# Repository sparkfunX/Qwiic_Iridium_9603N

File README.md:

# Qwiic Iridium 9603N

Iridium 9603N in Qwiic format (with I2C connectivity)

[Qwiic Iridium 9603N (SPX-16394)](https://www.sparkfun.com/products/16394)

## Repository Contents

- **/Hardware** - Eagle PCB, SCH and LBR design files
- **/Firmware** - Arduino code which comes pre-programmed onto the board
- **LEARN.md** contains a description of the Qwiic Iridium 9603N hardware
- **LICENSE.md** contains the licence information

## Arduino Examples

You will find a complete set of Arduino Examples for the Qwiic Iridium 9603N built into the [SparkFun IridiumSBD I2C Arduino Library](https://github.com/sparkfun/SparkFun_IridiumSBD_I2C_Arduino_Library).
Look for the [I2C_Examples__Qwiic_Iridium](https://github.com/sparkfun/SparkFun_IridiumSBD_I2C_Arduino_Library/tree/master/examples).

## Acknowledgements

This project relies upon [Spence Konde's ATTinyCore](https://github.com/SpenceKonde/ATTinyCore) for the ATtiny841.
Spence's work is gratefully acknowledged.

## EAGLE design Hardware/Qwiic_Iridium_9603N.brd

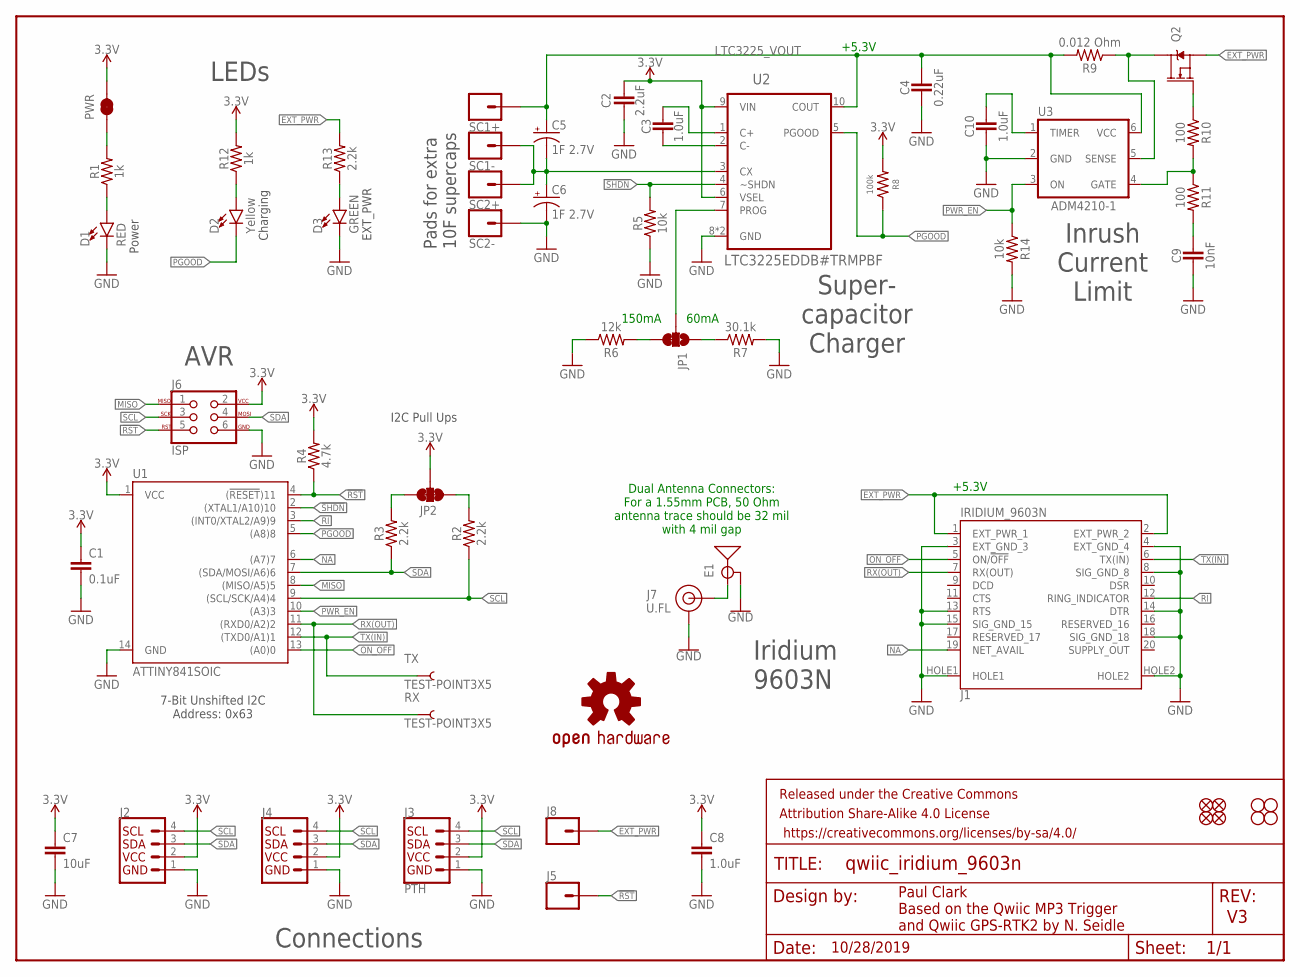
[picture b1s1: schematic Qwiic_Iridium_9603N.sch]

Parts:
C1: 0.1uF; 0603
C2: 2.2uF; 0603
C3, C8, C10: 1.0uF; 0603
C4: 0.22uF; 0603
C5, C6: 1F 2.7V; CPOL-RADIAL-1F-2.7V
C7: 10uF; 0603
C9: 10nF; 0603
D1: RED; LED-0603
D2: Yellow; LED-0603
D3: GREEN; LED-0603
E1: ANTENNA-GROUNDEDEDGE_SMA; SMA-EDGE
FRAME1: FRAME-LETTER; CREATIVE_COMMONS
J1: IRIDIUM_9603N
J2, J4: QWIIC_CONNECTORJS-1MM; JST04_1MM_RA
J3: PTH; 1X04_NO_SILK
J5, J8: CONN_01PTH_NO_SILK_YES_STOP; 1X01_NO_SILK
J6: ISP; 2X3_TEST_POINTS
J7: U.FL
JP1: JUMPER-SMT_3_1-NC_TRACE_SILK; SMT-JUMPER_3_1-NC_TRACE_SILK
JP2: JUMPER-SMT_3_2-NC_TRACE_SILK; SMT-JUMPER_3_2-NC_TRACE_SILK
JP3, JP4, JP9, JP10: STAND-OFF
JP5, JP6, JP7, JP8: FIDUCIAL1X2; FIDUCIAL-1X2
LOGO1: OSHW-LOGOMINI; OSHW-LOGO-MINI
PWR: JUMPER-SMT_2_NC_TRACE_SILK; SMT-JUMPER_2_NC_TRACE_SILK
Q2: 5.8A/30V/35mΩ; SOT23-3
R1, R12: 1k; 0603
R2, R3, R13: 2.2k; 0603
R4: 4.7k; 0603
R5, R14: 10k; 0603
R6: 12k; 0603
R7: 30.1k; 0603
R8: 100k; 0603
R9: 0.012 Ohm; 0603
R10, R11: 100; 0603
RX: TEST-POINT3X5; PAD.03X.05
SC1+, SC1-, SC2+, SC2-: CONN_01PTH_NO_SILK_YES_STOP; 1X01_NO_SILK
TX: TEST-POINT3X5; PAD.03X.05
U1: ATTINY841SOIC; ATTINY841
U2: LTC3225EDDB#TRMPBF; DFN300X200-10L
U3: ADM4210-1; TSOT6

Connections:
3.3V: C1.1, C2.1, C7.1, C8.1, J2.2, J3.2 (VCC), J4.2, J6.2, JP2.2, PWR.2, R4.2, R8.2, R12.2, U1.1 (VCC), U2.6 (VSEL), U2.9 (VIN)
!RST: J5.1, J6.5, R4.1, U1.4 ((!RESET!)11)
!SHDN: R5.2, U1.2 ((XTAL1/A10)10), U2.4 (~SHDN)
EXT_PWR: J1.1 (EXT_PWR_1), J1.2 (EXT_PWR_2), J8.1, Q2.2 (S), R13.2
GND: C1.2, C2.2, C4.2, C6.-, C7.2, C8.2, C9.2, C10.2, D1.C, D3.C, E1.GND@0 (GND), E1.GND@1 (GND), E1.GND@2 (GND), E1.GND@3 (GND), J1.3 (EXT_GND_3), J1.4 (EXT_GND_4), J1.8 (SIG_GND_8), J1.13 (RTS), J1.14 (DTR), J1.15 (SIG_GND_15), J1.18 (SIG_GND_18), J1.HOLE1, J1.HOLE2, J2.1, J3.1 (GND), J4.1, J6.6, J7.1 (GND), J7.2 (GND), R5.1, R6.1, R7.2, R14.2, SC2-.1, U1.14 (GND), U2.8 (GND), U2.11 (GND), U3.2 (GND)
LTC3225_VOUT: C4.1, C5.+, R9.2, SC1+.1, U2.10 (COUT), U3.6 (VCC)
MISO: J6.1, U1.8 ((MISO/A5)5)
unnamed: C5.-, C6.+, SC1-.1, SC2+.1, U2.3 (CX)
unnamed: JP1.3, R6.2
unnamed: D1.A, R1.1
unnamed: JP1.1, R7.1
unnamed: D2.A, R12.1
unnamed: D3.A, R13.1
unnamed: E1.SIG (SIGNAL), J7.FEED (SIGNAL)
unnamed: Q2.3 (D), R9.1, U3.5 (SENSE)
unnamed: C3.2, U2.2 (C-)
unnamed: C3.1, U2.1 (C+)
unnamed: JP1.2, U2.7 (PROG)
unnamed: Q2.1 (G), R10.1
unnamed: R10.2, R11.1, U3.4 (GATE)
unnamed: C9.1, R11.2
unnamed: C10.1, U3.1 (TIMER)
unnamed: PWR.1, R1.2
NA: J1.19 (NET_AVAIL), U1.6 ((A7)7)
ON_OFF: J1.5 (ON/!OFF!), U1.13 ((A0)0)
PGOOD: D2.C, R8.1, U1.5 ((A8)8), U2.5 (PGOOD)
PWR_EN: R14.1, U1.10 ((A3)3), U3.3 (ON)
RI: J1.12 (RING_INDICATOR), U1.3 ((INT0/XTAL2/A9)9)
RX(OUT): J1.7 (RX(OUT)), RX.P$1, U1.11 ((RXD0/A2)2)
SCL: J2.4, J3.4 (SCL), J4.4, J6.3, R2.1, U1.9 ((SCL/SCK/A4)4)
SCL_PU1: JP2.1, R2.2
SDA: J2.3, J3.3 (SDA), J4.3, J6.4, R3.1, U1.7 ((SDA/MOSI/A6)6)
SDA_PU1: JP2.3, R3.2
TX(IN): J1.6 (TX(IN)), TX.P$1, U1.12 ((TXD0/A1)1)

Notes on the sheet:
Paul Clark Based on the Qwiic MP3 Trigger and Qwiic GPS-RTK2 by N. Seidle
Power
7-Bit Unshifted I2C Address: 0x63
I2C Pull Ups
AVR
Connections
+5.3V
150mA
60mA
Pads for extra 10F supercaps
Super- capacitor Charger
Charging
EXT_PWR
Iridium 9603N
Dual Antenna Connectors: For a 1.55mm PCB, 50 Ohm antenna trace should be 32 mil with 4 mil gap
LEDs
Inrush Current Limit
10/28/2019

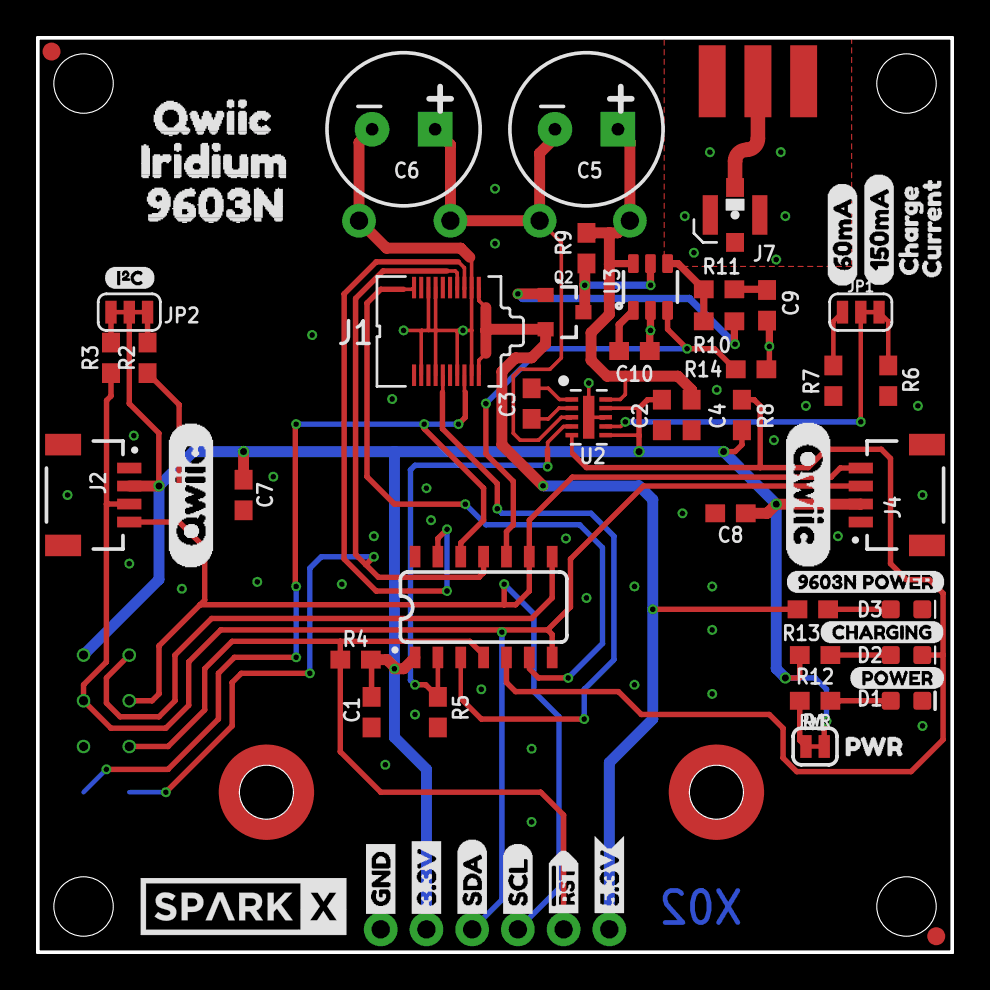
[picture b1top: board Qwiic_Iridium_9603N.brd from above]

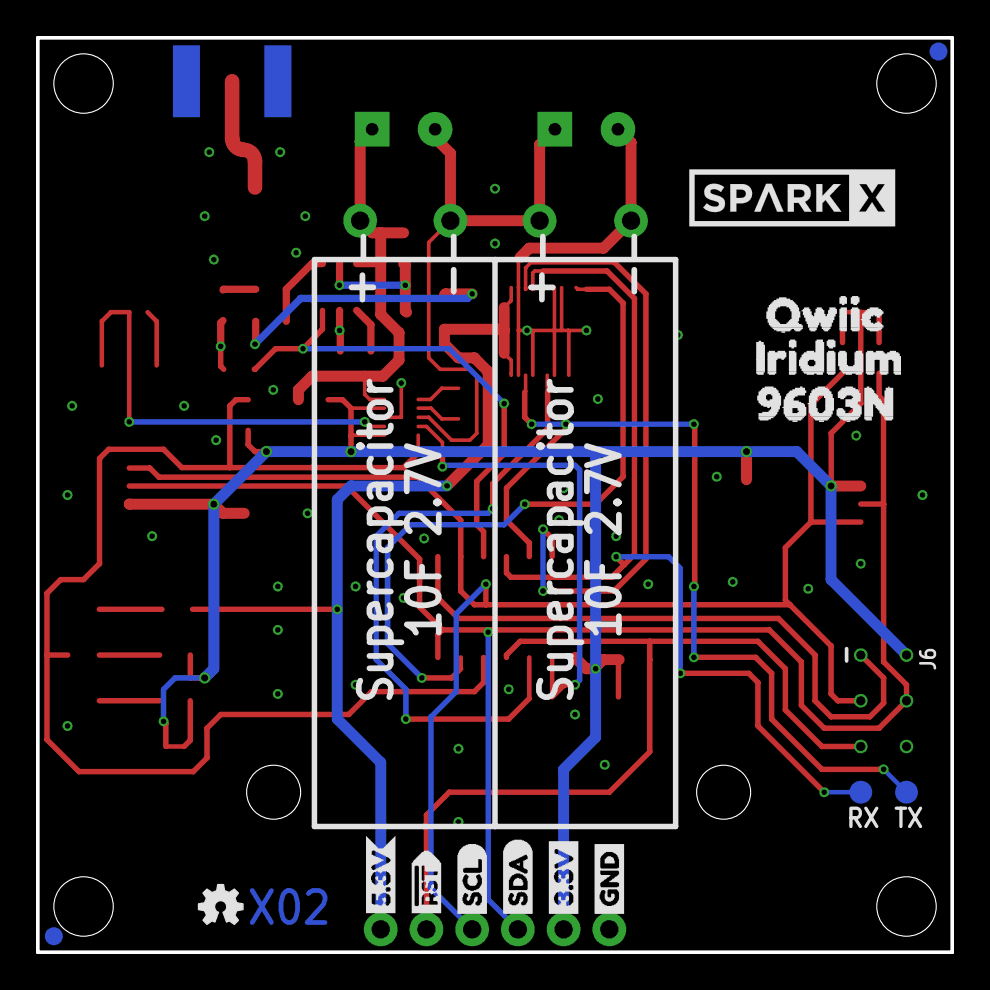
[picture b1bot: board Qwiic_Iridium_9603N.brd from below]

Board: 2 copper layers, 50.8 x 50.8 mm, 90 parts (16 on the bottom side), 34 nets.

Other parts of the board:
U$1: 60MA0
U$2: POWER0
U$3, U$22: GND1
U$4, U$21: 3#3V2
U$5, U$27: SDA8
U$6, U$26: SCL9
U$7, U$16: RST#-[>
U$8: I_SUPER2_C-()-03
U$9: CHARGING0
U$10: 9603N_POWER0
U$11, U$32: 5#3V0
U$12, U$17, U$23, U$25: QWIIC0
U$13: 150MA0
U$14: CHARGE0
U$15: CURRENT0
U$18, U$19: IRIDIUM0
U$20, U$24: 9603N0
U$29, U$30: SPARKX-LARGE
U$31: _PWR1

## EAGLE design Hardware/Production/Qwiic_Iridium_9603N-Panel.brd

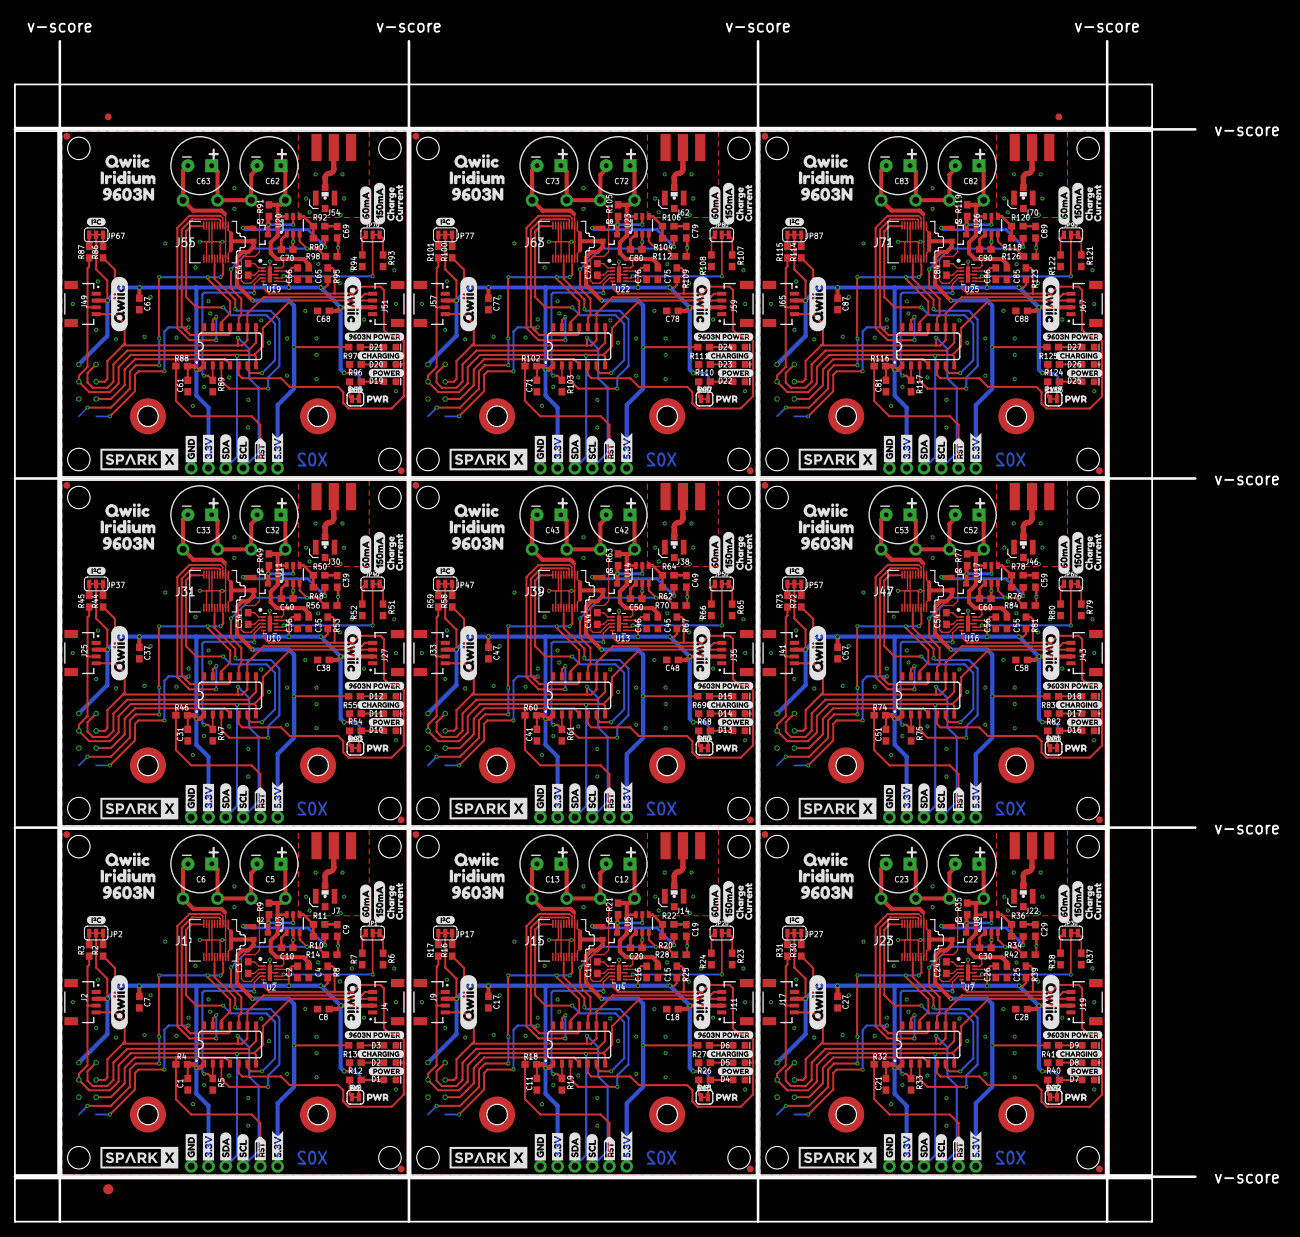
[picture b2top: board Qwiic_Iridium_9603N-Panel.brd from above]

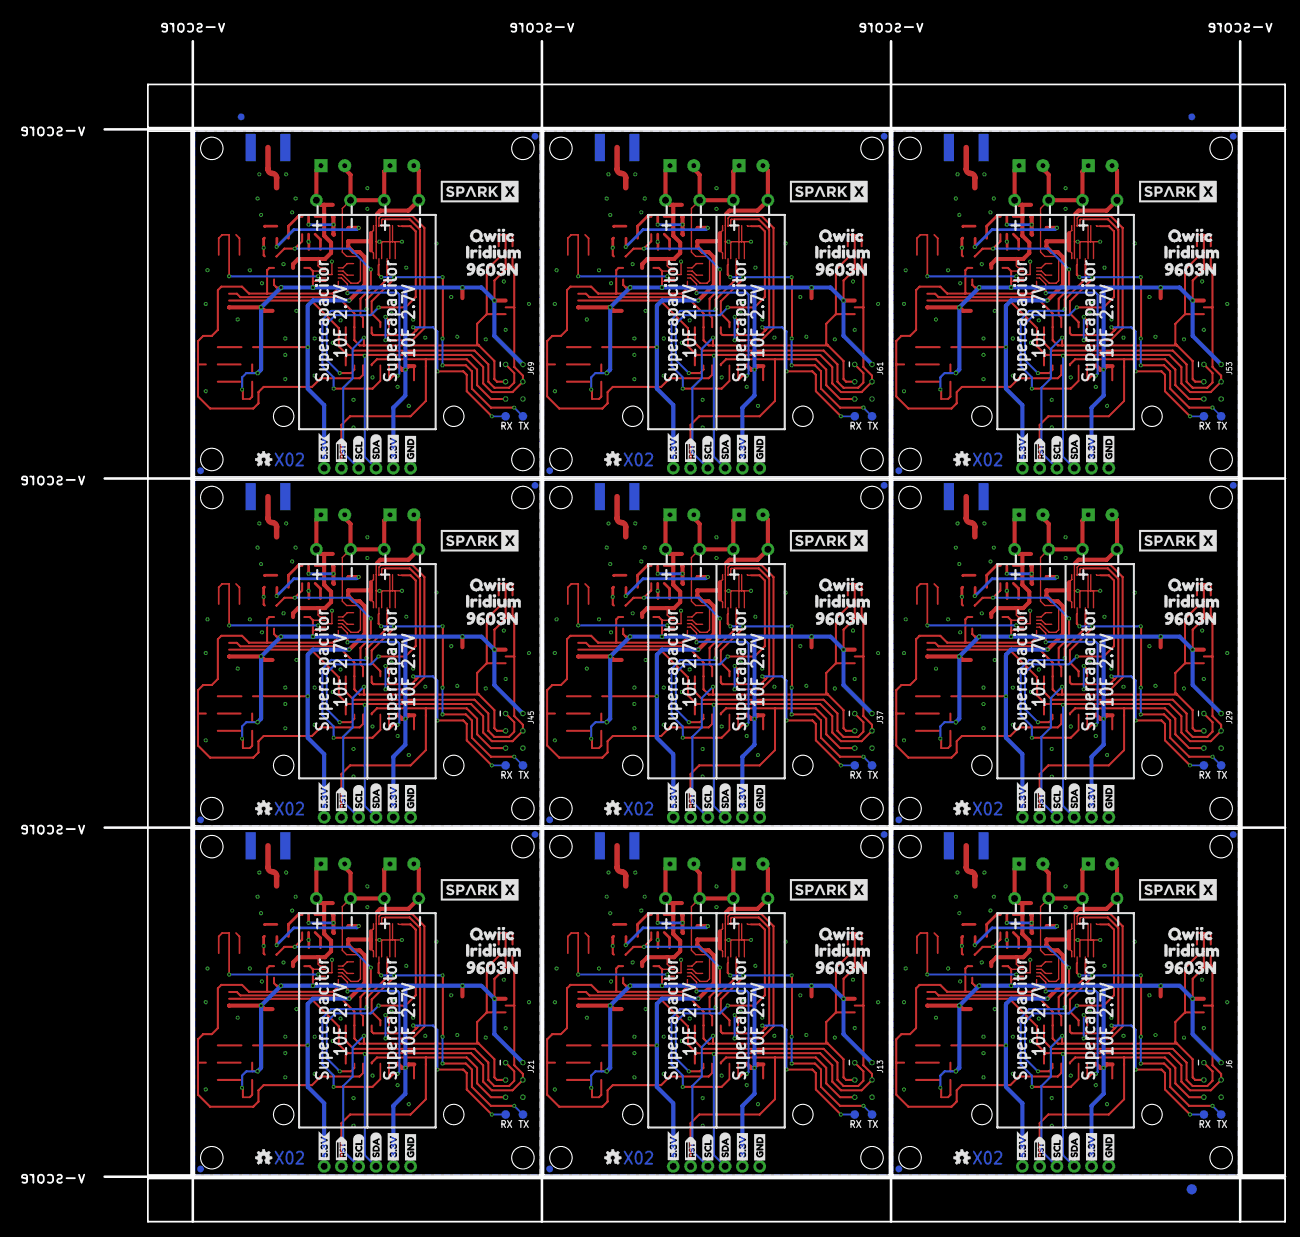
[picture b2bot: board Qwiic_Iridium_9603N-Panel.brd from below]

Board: 2 copper layers, 186.7 x 177.4 mm, 807 parts (147 on the bottom side), 306 nets.

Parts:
C1, C11, C21, C31, C41, C51, C61, C71, C81: 0.1uF; 0603
C2, C16, C26, C36, C46, C56, C66, C76, C86: 2.2uF; 0603
C3, C8, C10, C14, C18, C20, C24, C28, C30, C34, C38, C40, C44, C48, C50, C54, C58, C60, C64, C68, C70, C74, C78, C80, C84, C88, C90: 1.0uF; 0603
C4, C15, C25, C35, C45, C55, C65, C75, C85: 0.22uF; 0603
C5, C6, C12, C13, C22, C23, C32, C33, C42, C43, C52, C53, C62, C63, C72, C73, C82, C83: 1F 2.7V; CPOL-RADIAL-1F-2.7V
C7, C17, C27, C37, C47, C57, C67, C77, C87: 10uF; 0603
C9, C19, C29, C39, C49, C59, C69, C79, C89: 10nF; 0603
D1, D4, D7, D10, D13, D16, D19, D22, D25: RED; LED-0603
D2, D5, D8, D11, D14, D17, D20, D23, D26: Yellow; LED-0603
D3, D6, D9, D12, D15, D18, D21, D24, D27: GREEN; LED-0603
E1, E2, E3, E4, E5, E6, E7, E8, E9: ANTENNA-GROUNDEDEDGE_SMA; SMA-EDGE
E$1, E$2, E$3, E$4: FIDUCIAL-1X2
E$5, E$6: FIDUCIAL-1.5X3
J1, J15, J23, J31, J39, J47, J55, J63, J71: IRIDIUM_9603N
J2, J4, J9, J11, J17, J19, J25, J27, J33, J35, J41, J43, J49, J51, J57, J59, J65, J67: JST04_1MM_RA
J3, J10, J18, J26, J34, J42, J50, J58, J66: PTH; 1X04_NO_SILK
J5, J8, J12, J16, J20, J24, J28, J32, J36, J40, J44, J48, J52, J56, J60, J64, J68, J72: 1X01_NO_SILK
J6, J13, J21, J29, J37, J45, J53, J61, J69: ISP; 2X3_TEST_POINTS
J7, J14, J22, J30, J38, J46, J54, J62, J70: U.FL
JP1, JP20, JP30, JP40, JP50, JP60, JP70, JP80, JP90: JUMPER-SMT_3_1-NC_TRACE_SILK; SMT-JUMPER_3_1-NC_TRACE_SILK
JP2, JP17, JP27, JP37, JP47, JP57, JP67, JP77, JP87: JUMPER-SMT_3_2-NC_TRACE_SILK; SMT-JUMPER_3_2-NC_TRACE_SILK
JP3, JP4, JP9, JP10, JP11, JP12, JP18, JP19, JP21, JP22, JP28, JP29, JP31, JP32, JP38, JP39, JP41, JP42, JP48, JP49, JP51, JP52, JP58, JP59, JP61, JP62, JP68, JP69, JP71, JP72, JP78, JP79, JP81, JP82, JP88, JP89: STAND-OFF
JP5, JP6, JP7, JP8, JP13, JP14, JP15, JP16, JP23, JP24, JP25, JP26, JP33, JP34, JP35, JP36, JP43, JP44, JP45, JP46, JP53, JP54, JP55, JP56, JP63, JP64, JP65, JP66, JP73, JP74, JP75, JP76, JP83, JP84, JP85, JP86: FIDUCIAL1X2; FIDUCIAL-1X2
LOGO1, LOGO2, LOGO3, LOGO4, LOGO5, LOGO6, LOGO7, LOGO8, LOGO9: OSHW-LOGOMINI; OSHW-LOGO-MINI
PWR, PWR1, PWR2, PWR3, PWR4, PWR5, PWR6, PWR7, PWR8: JUMPER-SMT_2_NC_TRACE_SILK; SMT-JUMPER_2_NC_TRACE_SILK
Q1, Q2, Q3, Q4, Q5, Q6, Q7, Q8, Q9: 5.8A/30V/35mΩ; SOT23-3
R1, R12, R15, R26, R29, R40, R43, R54, R57, R68, R71, R82, R85, R96, R99, R110, R113, R124: 1k; 0603
R2, R3, R13, R16, R17, R27, R30, R31, R41, R44, R45, R55, R58, R59, R69, R72, R73, R83, R86, R87, R97, R100, R101, R111, R114, R115, R125: 2.2k; 0603
R4, R18, R32, R46, R60, R74, R88, R102, R116: 4.7k; 0603
R5, R14, R19, R28, R33, R42, R47, R56, R61, R70, R75, R84, R89, R98, R103, R112, R117, R126: 10k; 0603
R6, R23, R37, R51, R65, R79, R93, R107, R121: 12k; 0603
R7, R24, R38, R52, R66, R80, R94, R108, R122: 30.1k; 0603
R8, R25, R39, R53, R67, R81, R95, R109, R123: 100k; 0603
R9, R21, R35, R49, R63, R77, R91, R105, R119: 0.012 Ohm; 0603
R10, R11, R20, R22, R34, R36, R48, R50, R62, R64, R76, R78, R90, R92, R104, R106, R118, R120: 100; 0603
RX, RX1, RX2, RX3, RX4, RX5, RX6, RX7, RX8: TEST-POINT3X5; PAD.03X.05
SC1+, SC1+1, SC1+2, SC1+3, SC1+4, SC1+5, SC1+6, SC1+7, SC1+8, SC1-, SC1-1, SC1-2, SC1-3, SC1-4, SC1-5, SC1-6, SC1-7, SC1-8, SC2+, SC2+1, SC2+2, SC2+3, SC2+4, SC2+5, SC2+6, SC2+7, SC2+8, SC2-, SC2-1, SC2-2, SC2-3, SC2-4, SC2-5, SC2-6, SC2-7, SC2-8: 1X01_NO_SILK
TX, TX1, TX2, TX3, TX4, TX5, TX6, TX7, TX8: TEST-POINT3X5; PAD.03X.05
U1, U6, U9, U12, U15, U18, U21, U24, U27: ATTINY841SOIC; ATTINY841
U2, U4, U7, U10, U13, U16, U19, U22, U25: LTC3225EDDB#TRMPBF; DFN300X200-10L
U3, U5, U8, U11, U14, U17, U20, U23, U26: ADM4210-1; TSOT6
U$1, U$46, U$77, U$108, U$139, U$170, U$201, U$232, U$263: 60MA0
U$2, U$43, U$74, U$105, U$136, U$167, U$198, U$229, U$260: POWER0
U$3, U$22, U$33, U$36, U$64, U$67, U$95, U$98, U$126, U$129, U$157, U$160, U$188, U$191, U$219, U$222, U$250, U$253: GND1
U$4, U$21, U$28, U$37, U$63, U$68, U$94, U$99, U$125, U$130, U$156, U$161, U$187, U$192, U$218, U$223, U$249, U$254: 3#3V2
U$5, U$27, U$35, U$38, U$66, U$69, U$97, U$100, U$128, U$131, U$159, U$162, U$190, U$193, U$221, U$224, U$252, U$255: SDA8
U$6, U$26, U$34, U$39, U$65, U$70, U$96, U$101, U$127, U$132, U$158, U$163, U$189, U$194, U$220, U$225, U$251, U$256: SCL9
U$7, U$16, U$41, U$42, U$72, U$73, U$103, U$104, U$134, U$135, U$165, U$166, U$196, U$197, U$227, U$228, U$258, U$259: RST#-[>
U$8, U$40, U$71, U$102, U$133, U$164, U$195, U$226, U$257: I_SUPER2_C-()-03
U$9, U$44, U$75, U$106, U$137, U$168, U$199, U$230, U$261: CHARGING0
U$10, U$45, U$76, U$107, U$138, U$169, U$200, U$231, U$262: 9603N_POWER0
U$11, U$32, U$61, U$62, U$92, U$93, U$123, U$124, U$154, U$155, U$185, U$186, U$216, U$217, U$247, U$248, U$278, U$279: 5#3V0
U$12, U$17, U$23, U$25, U$50, U$51, U$56, U$57, U$81, U$82, U$87, U$88, U$112, U$113, U$118, U$119, U$143, U$144, U$149, U$150, U$174, U$175, U$180, U$181, U$205, U$206, U$211, U$212, U$236, U$237, U$242, U$243, U$267, U$268, U$273, U$274: QWIIC0
U$13, U$47, U$78, U$109, U$140, U$171, U$202, U$233, U$264: 150MA0
U$14, U$48, U$79, U$110, U$141, U$172, U$203, U$234, U$265: CHARGE0
U$15, U$49, U$80, U$111, U$142, U$173, U$204, U$235, U$266: CURRENT0
U$18, U$19, U$52, U$53, U$83, U$84, U$114, U$115, U$145, U$146, U$176, U$177, U$207, U$208, U$238, U$239, U$269, U$270: IRIDIUM0
U$20, U$24, U$54, U$55, U$85, U$86, U$116, U$117, U$147, U$148, U$178, U$179, U$209, U$210, U$240, U$241, U$271, U$272: 9603N0
U$29, U$30, U$58, U$59, U$89, U$90, U$120, U$121, U$151, U$152, U$182, U$183, U$213, U$214, U$244, U$245, U$275, U$276: SPARKX-LARGE
U$31, U$60, U$91, U$122, U$153, U$184, U$215, U$246, U$277: _PWR1

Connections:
3.3V: C1.1, C2.1, C7.1, C8.1, J2.2, J3.2, J4.2, J6.2, JP2.2, PWR.2, R4.2, R8.2, R12.2, U1.1, U2.6, U2.9
3.3V1: C11.1, C16.1, C17.1, C18.1, J9.2, J10.2, J11.2, J13.2, JP17.2, PWR1.2, R18.2, R25.2, R26.2, U4.6, U4.9, U6.1
3.3V2: C21.1, C26.1, C27.1, C28.1, J17.2, J18.2, J19.2, J21.2, JP27.2, PWR2.2, R32.2, R39.2, R40.2, U7.6, U7.9, U9.1
3.3V3: C31.1, C36.1, C37.1, C38.1, J25.2, J26.2, J27.2, J29.2, JP37.2, PWR3.2, R46.2, R53.2, R54.2, U10.6, U10.9, U12.1
3.3V4: C41.1, C46.1, C47.1, C48.1, J33.2, J34.2, J35.2, J37.2, JP47.2, PWR4.2, R60.2, R67.2, R68.2, U13.6, U13.9, U15.1
3.3V5: C51.1, C56.1, C57.1, C58.1, J41.2, J42.2, J43.2, J45.2, JP57.2, PWR5.2, R74.2, R81.2, R82.2, U16.6, U16.9, U18.1
3.3V6: C61.1, C66.1, C67.1, C68.1, J49.2, J50.2, J51.2, J53.2, JP67.2, PWR6.2, R88.2, R95.2, R96.2, U19.6, U19.9, U21.1
3.3V7: C71.1, C76.1, C77.1, C78.1, J57.2, J58.2, J59.2, J61.2, JP77.2, PWR7.2, R102.2, R109.2, R110.2, U22.6, U22.9, U24.1
3.3V8: C81.1, C86.1, C87.1, C88.1, J65.2, J66.2, J67.2, J69.2, JP87.2, PWR8.2, R116.2, R123.2, R124.2, U25.6, U25.9, U27.1
!RST: J5.1, J6.5, R4.1, U1.4
!RST1: J12.1, J13.5, R18.1, U6.4
!RST2: J20.1, J21.5, R32.1, U9.4
!RST3: J28.1, J29.5, R46.1, U12.4
!RST4: J36.1, J37.5, R60.1, U15.4
!RST5: J44.1, J45.5, R74.1, U18.4
!RST6: J52.1, J53.5, R88.1, U21.4
!RST7: J60.1, J61.5, R102.1, U24.4
!RST8: J68.1, J69.5, R116.1, U27.4
!SHDN: R5.2, U1.2, U2.4
!SHDN1: R19.2, U4.4, U6.2
!SHDN2: R33.2, U7.4, U9.2
!SHDN3: R47.2, U10.4, U12.2
!SHDN4: R61.2, U13.4, U15.2
!SHDN5: R75.2, U16.4, U18.2
!SHDN6: R89.2, U19.4, U21.2
!SHDN7: R103.2, U22.4, U24.2
!SHDN8: R117.2, U25.4, U27.2
EXT_PWR: J1.1, J1.2, J8.1, Q2.2, R13.2
EXT_PWR1: J15.1, J15.2, J16.1, Q1.2, R27.2
EXT_PWR2: J23.1, J23.2, J24.1, Q3.2, R41.2
EXT_PWR3: J31.1, J31.2, J32.1, Q4.2, R55.2
EXT_PWR4: J39.1, J39.2, J40.1, Q5.2, R69.2
EXT_PWR5: J47.1, J47.2, J48.1, Q6.2, R83.2
EXT_PWR6: J55.1, J55.2, J56.1, Q7.2, R97.2
EXT_PWR7: J63.1, J63.2, J64.1, Q8.2, R111.2
EXT_PWR8: J71.1, J71.2, J72.1, Q9.2, R125.2
GND: C1.2, C2.2, C4.2, C6.-, C7.2, C8.2, C9.2, C10.2, D1.C, D3.C, E1.GND@0, E1.GND@1, E1.GND@2, E1.GND@3, J1.3, J1.4, J1.8, J1.13, J1.14, J1.15, J1.18, J1.HOLE1, J1.HOLE2, J2.1, J3.1, J4.1, J6.6, J7.1, J7.2, R5.1, R6.1, R7.2, R14.2, SC2-.1, U1.14, U2.8, U2.11, U3.2
GND1: C11.2, C13.-, C15.2, C16.2, C17.2, C18.2, C19.2, C20.2, D4.C, D6.C, E2.GND@0, E2.GND@1, E2.GND@2, E2.GND@3, J9.1, J10.1, J11.1, J13.6, J14.1, J14.2, J15.3, J15.4, J15.8, J15.13, J15.14, J15.15, J15.18, J15.HOLE1, J15.HOLE2, R19.1, R23.1, R24.2, R28.2, SC2-1.1, U4.8, U4.11, U5.2, U6.14
GND2: C21.2, C23.-, C25.2, C26.2, C27.2, C28.2, C29.2, C30.2, D7.C, D9.C, E3.GND@0, E3.GND@1, E3.GND@2, E3.GND@3, J17.1, J18.1, J19.1, J21.6, J22.1, J22.2, J23.3, J23.4, J23.8, J23.13, J23.14, J23.15, J23.18, J23.HOLE1, J23.HOLE2, R33.1, R37.1, R38.2, R42.2, SC2-2.1, U7.8, U7.11, U8.2, U9.14
GND3: C31.2, C33.-, C35.2, C36.2, C37.2, C38.2, C39.2, C40.2, D10.C, D12.C, E4.GND@0, E4.GND@1, E4.GND@2, E4.GND@3, J25.1, J26.1, J27.1, J29.6, J30.1, J30.2, J31.3, J31.4, J31.8, J31.13, J31.14, J31.15, J31.18, J31.HOLE1, J31.HOLE2, R47.1, R51.1, R52.2, R56.2, SC2-3.1, U10.8, U10.11, U11.2, U12.14
GND4: C41.2, C43.-, C45.2, C46.2, C47.2, C48.2, C49.2, C50.2, D13.C, D15.C, E5.GND@0, E5.GND@1, E5.GND@2, E5.GND@3, J33.1, J34.1, J35.1, J37.6, J38.1, J38.2, J39.3, J39.4, J39.8, J39.13, J39.14, J39.15, J39.18, J39.HOLE1, J39.HOLE2, R61.1, R65.1, R66.2, R70.2, SC2-4.1, U13.8, U13.11, U14.2, U15.14
GND5: C51.2, C53.-, C55.2, C56.2, C57.2, C58.2, C59.2, C60.2, D16.C, D18.C, E6.GND@0, E6.GND@1, E6.GND@2, E6.GND@3, J41.1, J42.1, J43.1, J45.6, J46.1, J46.2, J47.3, J47.4, J47.8, J47.13, J47.14, J47.15, J47.18, J47.HOLE1, J47.HOLE2, R75.1, R79.1, R80.2, R84.2, SC2-5.1, U16.8, U16.11, U17.2, U18.14
GND6: C61.2, C63.-, C65.2, C66.2, C67.2, C68.2, C69.2, C70.2, D19.C, D21.C, E7.GND@0, E7.GND@1, E7.GND@2, E7.GND@3, J49.1, J50.1, J51.1, J53.6, J54.1, J54.2, J55.3, J55.4, J55.8, J55.13, J55.14, J55.15, J55.18, J55.HOLE1, J55.HOLE2, R89.1, R93.1, R94.2, R98.2, SC2-6.1, U19.8, U19.11, U20.2, U21.14
GND7: C71.2, C73.-, C75.2, C76.2, C77.2, C78.2, C79.2, C80.2, D22.C, D24.C, E8.GND@0, E8.GND@1, E8.GND@2, E8.GND@3, J57.1, J58.1, J59.1, J61.6, J62.1, J62.2, J63.3, J63.4, J63.8, J63.13, J63.14, J63.15, J63.18, J63.HOLE1, J63.HOLE2, R103.1, R107.1, R108.2, R112.2, SC2-7.1, U22.8, U22.11, U23.2, U24.14
GND8: C81.2, C83.-, C85.2, C86.2, C87.2, C88.2, C89.2, C90.2, D25.C, D27.C, E9.GND@0, E9.GND@1, E9.GND@2, E9.GND@3, J65.1, J66.1, J67.1, J69.6, J70.1, J70.2, J71.3, J71.4, J71.8, J71.13, J71.14, J71.15, J71.18, J71.HOLE1, J71.HOLE2, R117.1, R121.1, R122.2, R126.2, SC2-8.1, U25.8, U25.11, U26.2, U27.14
LTC3225_VOUT: C4.1, C5.+, R9.2, SC1+.1, U2.10, U3.6
LTC3225_VOUT1: C12.+, C15.1, R21.2, SC1+1.1, U4.10, U5.6
LTC3225_VOUT2: C22.+, C25.1, R35.2, SC1+2.1, U7.10, U8.6
LTC3225_VOUT3: C32.+, C35.1, R49.2, SC1+3.1, U10.10, U11.6
LTC3225_VOUT4: C42.+, C45.1, R63.2, SC1+4.1, U13.10, U14.6
LTC3225_VOUT5: C52.+, C55.1, R77.2, SC1+5.1, U16.10, U17.6
LTC3225_VOUT6: C62.+, C65.1, R91.2, SC1+6.1, U19.10, U20.6
LTC3225_VOUT7: C72.+, C75.1, R105.2, SC1+7.1, U22.10, U23.6
LTC3225_VOUT8: C82.+, C85.1, R119.2, SC1+8.1, U25.10, U26.6
MISO: J6.1, U1.8
MISO1: J13.1, U6.8
MISO2: J21.1, U9.8
MISO3: J29.1, U12.8
MISO4: J37.1, U15.8
MISO5: J45.1, U18.8
MISO6: J53.1, U21.8
MISO7: J61.1, U24.8
MISO8: J69.1, U27.8
unnamed: C5.-, C6.+, SC1-.1, SC2+.1, U2.3
unnamed: JP1.3, R6.2
unnamed: D1.A, R1.1
unnamed: JP1.1, R7.1
unnamed: D2.A, R12.1
unnamed: D3.A, R13.1
unnamed: E1.SIG, J7.FEED
unnamed: Q2.3, R9.1, U3.5
unnamed: C3.2, U2.2
unnamed: C3.1, U2.1
unnamed: JP1.2, U2.7
unnamed: Q2.1, R10.1
unnamed: R10.2, R11.1, U3.4
unnamed: C9.1, R11.2
unnamed: C10.1, U3.1
unnamed: PWR.1, R1.2
unnamed: D4.A, R15.1
unnamed: C14.2, U4.2
unnamed: C14.1, U4.1
unnamed: JP20.2, U4.7
unnamed: C12.-, C13.+, SC1-1.1, SC2+1.1, U4.3
unnamed: JP20.3, R23.2
unnamed: JP20.1, R24.1
unnamed: D5.A, R26.1
unnamed: D6.A, R27.1
unnamed: E2.SIG, J14.FEED
unnamed: Q1.3, R21.1, U5.5
unnamed: Q1.1, R20.1
unnamed: R20.2, R22.1, U5.4
unnamed: C19.1, R22.2
unnamed: C20.1, U5.1
unnamed: PWR1.1, R15.2
unnamed: D7.A, R29.1
unnamed: C24.2, U7.2
unnamed: C24.1, U7.1
unnamed: JP30.2, U7.7
unnamed: C22.-, C23.+, SC1-2.1, SC2+2.1, U7.3
unnamed: JP30.3, R37.2
unnamed: JP30.1, R38.1
unnamed: D8.A, R40.1
unnamed: D9.A, R41.1
unnamed: E3.SIG, J22.FEED
unnamed: Q3.3, R35.1, U8.5
unnamed: Q3.1, R34.1
unnamed: R34.2, R36.1, U8.4
unnamed: C29.1, R36.2
unnamed: C30.1, U8.1
unnamed: PWR2.1, R29.2
unnamed: D10.A, R43.1
unnamed: C34.2, U10.2
unnamed: C34.1, U10.1
unnamed: JP40.2, U10.7
unnamed: C32.-, C33.+, SC1-3.1, SC2+3.1, U10.3
unnamed: JP40.3, R51.2
unnamed: JP40.1, R52.1
unnamed: D11.A, R54.1
unnamed: D12.A, R55.1
unnamed: E4.SIG, J30.FEED
unnamed: Q4.3, R49.1, U11.5
unnamed: Q4.1, R48.1
unnamed: R48.2, R50.1, U11.4
unnamed: C39.1, R50.2
unnamed: C40.1, U11.1
unnamed: PWR3.1, R43.2
unnamed: D13.A, R57.1
unnamed: C44.2, U13.2
unnamed: C44.1, U13.1
unnamed: JP50.2, U13.7
unnamed: C42.-, C43.+, SC1-4.1, SC2+4.1, U13.3
unnamed: JP50.3, R65.2
unnamed: JP50.1, R66.1
unnamed: D14.A, R68.1
unnamed: D15.A, R69.1
unnamed: E5.SIG, J38.FEED
unnamed: Q5.3, R63.1, U14.5
unnamed: Q5.1, R62.1
unnamed: R62.2, R64.1, U14.4
unnamed: C49.1, R64.2
unnamed: C50.1, U14.1
unnamed: PWR4.1, R57.2
unnamed: D16.A, R71.1
unnamed: C54.2, U16.2
unnamed: C54.1, U16.1
unnamed: JP60.2, U16.7
unnamed: C52.-, C53.+, SC1-5.1, SC2+5.1, U16.3
unnamed: JP60.3, R79.2
unnamed: JP60.1, R80.1
unnamed: D17.A, R82.1
unnamed: D18.A, R83.1
unnamed: E6.SIG, J46.FEED
unnamed: Q6.3, R77.1, U17.5
unnamed: Q6.1, R76.1
unnamed: R76.2, R78.1, U17.4
unnamed: C59.1, R78.2
unnamed: C60.1, U17.1
unnamed: PWR5.1, R71.2
unnamed: D19.A, R85.1
unnamed: C64.2, U19.2
unnamed: C64.1, U19.1
unnamed: JP70.2, U19.7
unnamed: C62.-, C63.+, SC1-6.1, SC2+6.1, U19.3
unnamed: JP70.3, R93.2
unnamed: JP70.1, R94.1
unnamed: D20.A, R96.1
unnamed: D21.A, R97.1
unnamed: E7.SIG, J54.FEED
unnamed: Q7.3, R91.1, U20.5
unnamed: Q7.1, R90.1
unnamed: R90.2, R92.1, U20.4
unnamed: C69.1, R92.2
unnamed: C70.1, U20.1
unnamed: PWR6.1, R85.2
unnamed: D22.A, R99.1
unnamed: C74.2, U22.2
unnamed: C74.1, U22.1
unnamed: JP80.2, U22.7
unnamed: C72.-, C73.+, SC1-7.1, SC2+7.1, U22.3
unnamed: JP80.3, R107.2
unnamed: JP80.1, R108.1
unnamed: D23.A, R110.1
unnamed: D24.A, R111.1
unnamed: E8.SIG, J62.FEED
unnamed: Q8.3, R105.1, U23.5
unnamed: Q8.1, R104.1
unnamed: R104.2, R106.1, U23.4
unnamed: C79.1, R106.2
unnamed: C80.1, U23.1
unnamed: PWR7.1, R99.2
unnamed: D25.A, R113.1
unnamed: C84.2, U25.2
unnamed: C84.1, U25.1
unnamed: JP90.2, U25.7
unnamed: C82.-, C83.+, SC1-8.1, SC2+8.1, U25.3
unnamed: JP90.3, R121.2
unnamed: JP90.1, R122.1
unnamed: D26.A, R124.1
unnamed: D27.A, R125.1
unnamed: E9.SIG, J70.FEED
unnamed: Q9.3, R119.1, U26.5
unnamed: Q9.1, R118.1
unnamed: R118.2, R120.1, U26.4
unnamed: C89.1, R120.2
unnamed: C90.1, U26.1
unnamed: PWR8.1, R113.2
NA: J1.19, U1.6
NA1: J15.19, U6.6
NA2: J23.19, U9.6
NA3: J31.19, U12.6
NA4: J39.19, U15.6
NA5: J47.19, U18.6
NA6: J55.19, U21.6
NA7: J63.19, U24.6
NA8: J71.19, U27.6
ON_OFF: J1.5, U1.13
ON_OFF1: J15.5, U6.13
ON_OFF2: J23.5, U9.13
ON_OFF3: J31.5, U12.13
ON_OFF4: J39.5, U15.13
ON_OFF5: J47.5, U18.13
ON_OFF6: J55.5, U21.13
ON_OFF7: J63.5, U24.13
ON_OFF8: J71.5, U27.13
PGOOD: D2.C, R8.1, U1.5, U2.5
PGOOD1: D5.C, R25.1, U4.5, U6.5
PGOOD2: D8.C, R39.1, U7.5, U9.5
PGOOD3: D11.C, R53.1, U10.5, U12.5
PGOOD4: D14.C, R67.1, U13.5, U15.5
PGOOD5: D17.C, R81.1, U16.5, U18.5
PGOOD6: D20.C, R95.1, U19.5, U21.5
PGOOD7: D23.C, R109.1, U22.5, U24.5
PGOOD8: D26.C, R123.1, U25.5, U27.5
PWR_EN: R14.1, U1.10, U3.3
PWR_EN1: R28.1, U5.3, U6.10
PWR_EN2: R42.1, U8.3, U9.10
PWR_EN3: R56.1, U11.3, U12.10
PWR_EN4: R70.1, U14.3, U15.10
PWR_EN5: R84.1, U17.3, U18.10
PWR_EN6: R98.1, U20.3, U21.10
PWR_EN7: R112.1, U23.3, U24.10
PWR_EN8: R126.1, U26.3, U27.10
RI: J1.12, U1.3
RI1: J15.12, U6.3
RI2: J23.12, U9.3
RI3: J31.12, U12.3
RI4: J39.12, U15.3
RI5: J47.12, U18.3
RI6: J55.12, U21.3
RI7: J63.12, U24.3
RI8: J71.12, U27.3
RX(OUT): J1.7, RX.P$1, U1.11
RX(OUT)1: J15.7, RX1.P$1, U6.11
RX(OUT)2: J23.7, RX2.P$1, U9.11
RX(OUT)3: J31.7, RX3.P$1, U12.11
RX(OUT)4: J39.7, RX4.P$1, U15.11
RX(OUT)5: J47.7, RX5.P$1, U18.11
RX(OUT)6: J55.7, RX6.P$1, U21.11
RX(OUT)7: J63.7, RX7.P$1, U24.11
RX(OUT)8: J71.7, RX8.P$1, U27.11
SCL: J2.4, J3.4, J4.4, J6.3, R2.1, U1.9
SCL1: J9.4, J10.4, J11.4, J13.3, R16.1, U6.9
SCL2: J17.4, J18.4, J19.4, J21.3, R30.1, U9.9
SCL3: J25.4, J26.4, J27.4, J29.3, R44.1, U12.9
SCL4: J33.4, J34.4, J35.4, J37.3, R58.1, U15.9
SCL5: J41.4, J42.4, J43.4, J45.3, R72.1, U18.9
SCL6: J49.4, J50.4, J51.4, J53.3, R86.1, U21.9
SCL7: J57.4, J58.4, J59.4, J61.3, R100.1, U24.9
SCL8: J65.4, J66.4, J67.4, J69.3, R114.1, U27.9
SCL_PU1: JP2.1, R2.2
SCL_PU2: JP17.1, R16.2
SCL_PU3: JP27.1, R30.2
SCL_PU4: JP37.1, R44.2
SCL_PU5: JP47.1, R58.2
SCL_PU6: JP57.1, R72.2
SCL_PU7: JP67.1, R86.2
SCL_PU8: JP77.1, R100.2
SCL_PU9: JP87.1, R114.2
SDA: J2.3, J3.3, J4.3, J6.4, R3.1, U1.7
SDA1: J9.3, J10.3, J11.3, J13.4, R17.1, U6.7
SDA2: J17.3, J18.3, J19.3, J21.4, R31.1, U9.7
SDA3: J25.3, J26.3, J27.3, J29.4, R45.1, U12.7
SDA4: J33.3, J34.3, J35.3, J37.4, R59.1, U15.7
SDA5: J41.3, J42.3, J43.3, J45.4, R73.1, U18.7
SDA6: J49.3, J50.3, J51.3, J53.4, R87.1, U21.7
SDA7: J57.3, J58.3, J59.3, J61.4, R101.1, U24.7
SDA8: J65.3, J66.3, J67.3, J69.4, R115.1, U27.7
SDA_PU1: JP2.3, R3.2
SDA_PU2: JP17.3, R17.2
SDA_PU3: JP27.3, R31.2
SDA_PU4: JP37.3, R45.2
SDA_PU5: JP47.3, R59.2
SDA_PU6: JP57.3, R73.2
SDA_PU7: JP67.3, R87.2
SDA_PU8: JP77.3, R101.2
SDA_PU9: JP87.3, R115.2
TX(IN): J1.6, TX.P$1, U1.12
TX(IN)1: J15.6, TX1.P$1, U6.12
TX(IN)2: J23.6, TX2.P$1, U9.12
TX(IN)3: J31.6, TX3.P$1, U12.12
TX(IN)4: J39.6, TX4.P$1, U15.12
TX(IN)5: J47.6, TX5.P$1, U18.12
TX(IN)6: J55.6, TX6.P$1, U21.12
TX(IN)7: J63.6, TX7.P$1, U24.12
TX(IN)8: J71.6, TX8.P$1, U27.12

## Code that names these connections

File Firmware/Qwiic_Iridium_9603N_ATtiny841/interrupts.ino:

// Qwiic Iridium 9603N interrupt routines

// I2C receiveEvent
// ================
// Handle a write to the IO pins or the Serial port
// If the first byte is IO_REG (0x10), read one more byte if present and write the contents to the IO pins.
// If the first byte is LEN_REG (0xFD), store it in last_address so we know what to do during the next requestEvent
// If the first byte is DATA_REG (0xFF), keep reading bytes (if any) and write them to the 9603 serial port.
void receiveEvent(int numberOfBytesReceived) {
  if (numberOfBytesReceived > 0) { // Check that we received some data (!) (hopefully redundant!)
    
    uint8_t incoming = Wire.read(); // Read the first byte
    last_address = incoming; // Store this byte in last_address so we know what to do during the next requestEvent

    if (incoming == IO_REG) { // Does the Master want to read or set the I/O pins?
      if (numberOfBytesReceived > 1) { // Did the Master send a second byte to set the I/O pins?
        uint8_t incoming2 = Wire.read(); // Read the second byte

        if (incoming2 & IO_SHDN) { // If the SHDN bit is ON
          digitalWrite(SHDN, SHDN__ON); // Turn the pin ON
        }
        else {
          digitalWrite(SHDN, SHDN__OFF); // Turn the pin OFF
        }
        
        if (incoming2 & IO_PWR_EN) { // If the PWR_EN bit is ON
          digitalWrite(PWR_EN, PWR_EN__ON); // Turn the pin ON
        }
        else {
          digitalWrite(PWR_EN, PWR_EN__OFF); // Turn the pin OFF
        }
        
        if (incoming2 & IO_ON_OFF) { // If the ON_OFF bit is ON
          digitalWrite(ON_OFF, ON_OFF__ON); // Turn the pin ON
        }
        else {
          digitalWrite(ON_OFF, ON_OFF__OFF); // Turn the pin OFF
        }
        
        if ((incoming2 & IO_RI) == 0x00) { // If the RI bit is clear
          RI_FLAG = false; // Clear the RI flag
        }
        
        LOW_POWER_MODE = ((incoming2 & IO_LOW_PWR) == IO_LOW_PWR); // Update low power mode
      }
      if (numberOfBytesReceived > 2) // Did we receive any unexpected extra data?
      {
        for (int i = 2; i < numberOfBytesReceived; i++) // If we did, mop up the extra bytes - hopefully redundant?!
        {
          Wire.read();
        }
      }
    }

    else if (incoming == DATA_REG) { // Does the Master want to write serial data to the 9603N?
      if (numberOfBytesReceived > 1) // If the Master sent any serial data, write it to the 9603 now
      {
        for (int i = 1; i < numberOfBytesReceived; i++)
        {
          uint8_t incoming2 = Wire.read();
          Serial.write(incoming2);
        }
      }
    }

    else if (incoming == LEN_REG) { // Does the Master want to read the available serial length?
      // We shouldn't need to do anything (except update last_address)
      if (numberOfBytesReceived > 1) // Did we receive any unexpected extra data?
      {
        for (int i = 1; i < numberOfBytesReceived; i++) // If we did, mop up the extra bytes - hopefully redundant?!
        {
          Wire.read();
        }
      }
    }
  }
  
  last_activity = millis(); // Update last_activity
}

// I2C requestEvent
// ================
// Handle a read of the IO pins or the Serial port
// If last_address was IO_REG (0x10) then return the status of the IO pins
// If last_address was LEN_REG (0xFD), return the MSB and LSB of the serial buffer length and store them in serAvailMSB/LSB
// If last_address was DATA_REG (0xFF), return up to SER_PACKET_SIZE bytes from the serial buffer and update serAvailMSB/LSB
void requestEvent()
{
  if (last_address == IO_REG) // Return the status of the IO pins
  {
    // Read the IO pins one at a time and set or clear bits in IO_REGISTER appropriately
    
    if (digitalRead(SHDN) == SHDN__ON) { // If the SHDN pin is in its ON state (not necessarily that it is HIGH)
      IO_REGISTER |= IO_SHDN; // Set the SHDN bit in IO_REGISTER
    }
    else {
      IO_REGISTER &= ~IO_SHDN; // Clear the SHDN bit in IO_REGISTER
    }
    
    if (digitalRead(PWR_EN) == PWR_EN__ON) { // If the PWR_EN pin is in its ON state (not necessarily that it is HIGH)
      IO_REGISTER |= IO_PWR_EN; // Set the PWR_EN bit in IO_REGISTER
    }
    else {
      IO_REGISTER &= ~IO_PWR_EN; // Clear the PWR_EN bit in IO_REGISTER
    }
    
    if (digitalRead(ON_OFF) == ON_OFF__ON) { // If the ON_OFF pin is in its ON state (not necessarily that it is HIGH)
      IO_REGISTER |= IO_ON_OFF; // Set the ON_OFF bit in IO_REGISTER
    }
    else {
      IO_REGISTER &= ~IO_ON_OFF; // Clear the ON_OFF bit in IO_REGISTER
    }
    
    if (RI_FLAG == true) { // If the RI_FLAG is true (set by the ISR)
      IO_REGISTER |= IO_RI; // Set the RI bit in IO_REGISTER
    }
    else {
      IO_REGISTER &= ~IO_RI; // Clear the RI bit in IO_REGISTER
    }
    
    if (digitalRead(NA) == NA__ON) { // If the NA pin is in its ON state (not necessarily that it is HIGH)
      IO_REGISTER |= IO_NA; // Set the NA bit in IO_REGISTER
    }
    else {
      IO_REGISTER &= ~IO_NA; // Clear the NA bit in IO_REGISTER
    }
    
    if (digitalRead(PGOOD) == PGOOD__ON) { // If the PGOOD pin is in its ON state (not necessarily that it is HIGH)
      IO_REGISTER |= IO_PGOOD; // Set the PGOOD bit in IO_REGISTER
    }
    else {
      IO_REGISTER &= ~IO_PGOOD; // Clear the PGOOD bit in IO_REGISTER
    }
  
    if (LOW_POWER_MODE) { // If low power mode is enabled
      IO_REGISTER |= IO_LOW_PWR; // Set the low power bit in IO_REGISTER
    }
    else {
      IO_REGISTER &= ~IO_LOW_PWR; // Clear the low power bit in IO_REGISTER
    }
  
    // Now write IO_REGISTER to I2C
    Wire.write(IO_REGISTER);

    // Reset last_address to zero
    last_address = 0;
  }

  else if (last_address == LEN_REG) // Return the MSB and LSB of the serial buffer length and store them in serAvailMSB/LSB
  {
    //Check how many bytes are available in the serial buffer
    uint16_t avail = Serial.available();
    
    //Store the MSB for the subsequent requestEvent
    serAvailMSB = (uint8_t)((avail & 0xFF00) >> 8);
    
    //Store the LSB for the subsequent  requestEvent
    serAvailLSB = (uint8_t)(avail & 0xFF);

    uint8_t buff[2];
    buff[0] = serAvailMSB;
    buff[1] = serAvailLSB;

    Wire.write(buff, 2); // Return the available bytes in MSB, LSB format

    // Reset last_address to zero
    last_address = 0;
  }

  else if (last_address == DATA_REG) // Return up to SER_PACKET_SIZE bytes from the serial buffer and update serAvailMSB/LSB
  {
    // Check how many bytes the Master is expecting us to send
    uint16_t avail = (((uint16_t)serAvailMSB) << 8) | (uint16_t)serAvailLSB;
    uint8_t buff[SER_PACKET_SIZE];
    if (avail > SER_PACKET_SIZE) // If there are more than SER_PACKET_SIZE bytes to write
    {
      avail = avail - SER_PACKET_SIZE; // Decrease the available bytes by SER_PACKET_SIZE
      // Update the number of available bytes and leave last_address set to DATA_REG
      serAvailMSB = (uint8_t)((avail & 0xFF00) >> 8);
      serAvailLSB = (uint8_t)(avail & 0xFF);
      for (int i = 0; i < SER_PACKET_SIZE; i++) // For each of the bytes
      {
        buff[i] = Serial.read(); // Read a byte from the serial buffer
      }
      Wire.write(buff, SER_PACKET_SIZE); // Write the bytes
    }
    else if (avail > 0) // If there are <= SER_PACKET_SIZE bytes left (but more than zero)
    {
      serAvailMSB = 0; // Zero the number of available bytes (redundant?)
      serAvailLSB = 0;
      for (int i = 0; i < avail; i++) // For each byte
      {
        buff[i] = Serial.read(); // Read a byte from the serial buffer
      }
      Wire.write(buff, avail); // Write the bytes
      last_address = 0; // Reset last_address to zero now all bytes have been written
    }
    else // If there are zero bytes to send - this should hopefully be redundant/impossible?
    {
      last_address = 0; // Reset last_address to zero
    }
  }

  last_activity = millis(); // Update last_activity
}

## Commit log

2020-05-30 Initial commit based on the PaulZC and SparkfunX repos
2020-06-01 Adding x02 regular and production files.
2020-06-01 X03 Candidate - adds standoffs as separate items for the BOM

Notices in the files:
parts and their libraries:
SparkFun-Resistors: Licensing: Creative Commons ShareAlike 4.0 International - https://creativecommons.org/licenses/by-sa/4.0
SparkFun-Aesthetics: Released under the Creative Commons Attribution Share-Alike 4.0 License
SparkFun-Aesthetics: https://creativecommons.org/licenses/by-sa/4.0
